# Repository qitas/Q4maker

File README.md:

# [Q4maker](https://github.com/qitas/Q4maker) 

自定义3D打印机版本，包括arduino的4喷头装置和STM32升级版本

相关资源参考：

* [Marlin](https://github.com/MuellerDominik/Marlin) 
* [硬件设计](https://github.com/mnemocron/FHNW-Pro4E-FS19T8-3DPrinterBoard-STM32) 

## 锻造最美之器

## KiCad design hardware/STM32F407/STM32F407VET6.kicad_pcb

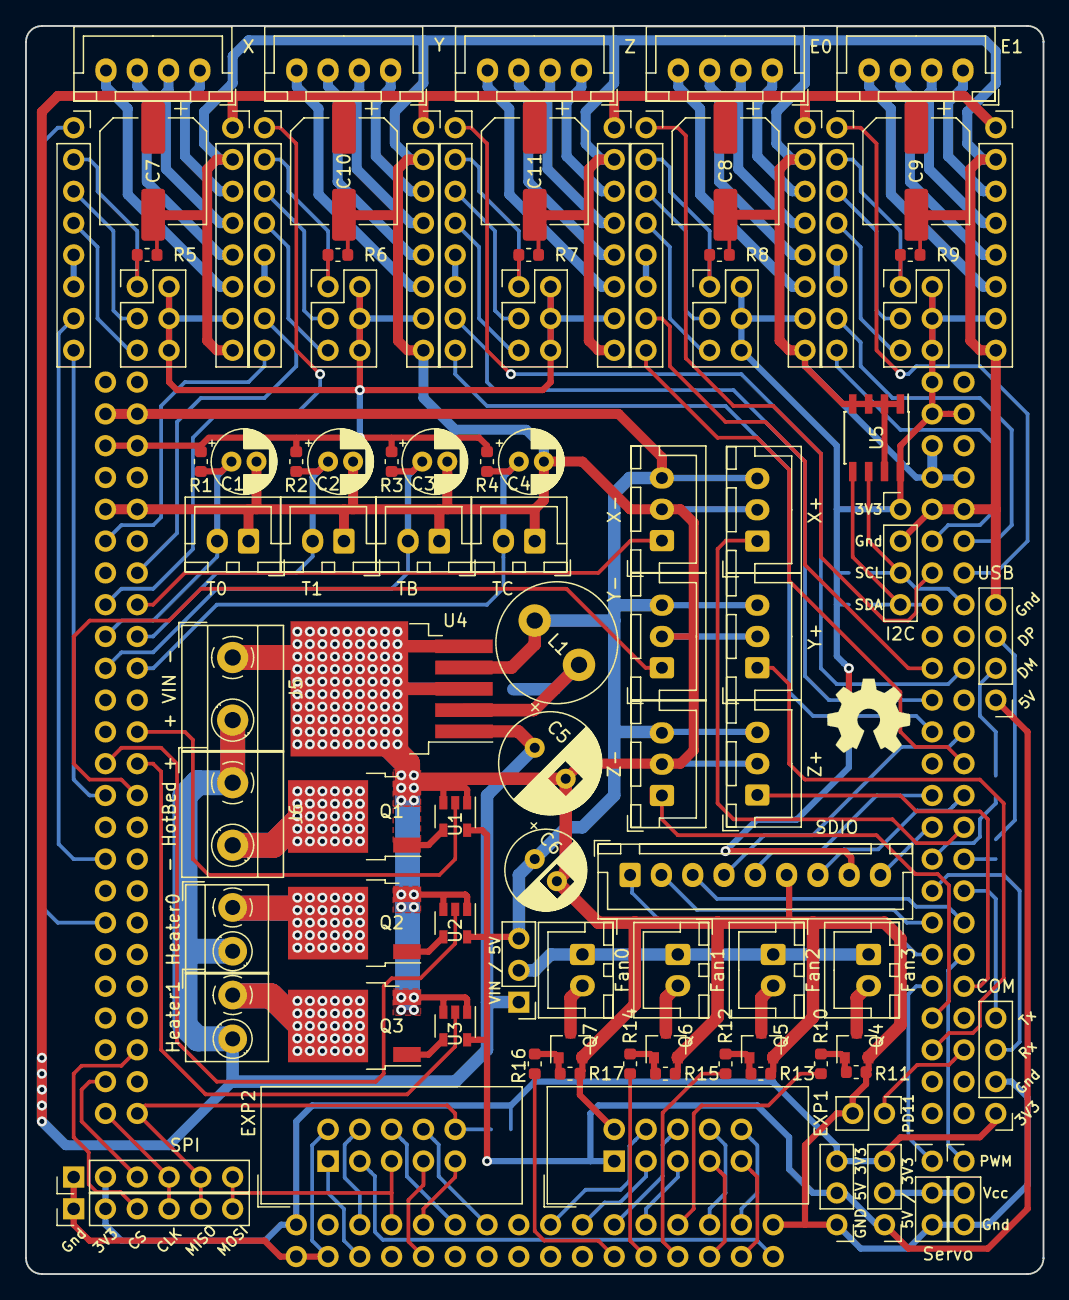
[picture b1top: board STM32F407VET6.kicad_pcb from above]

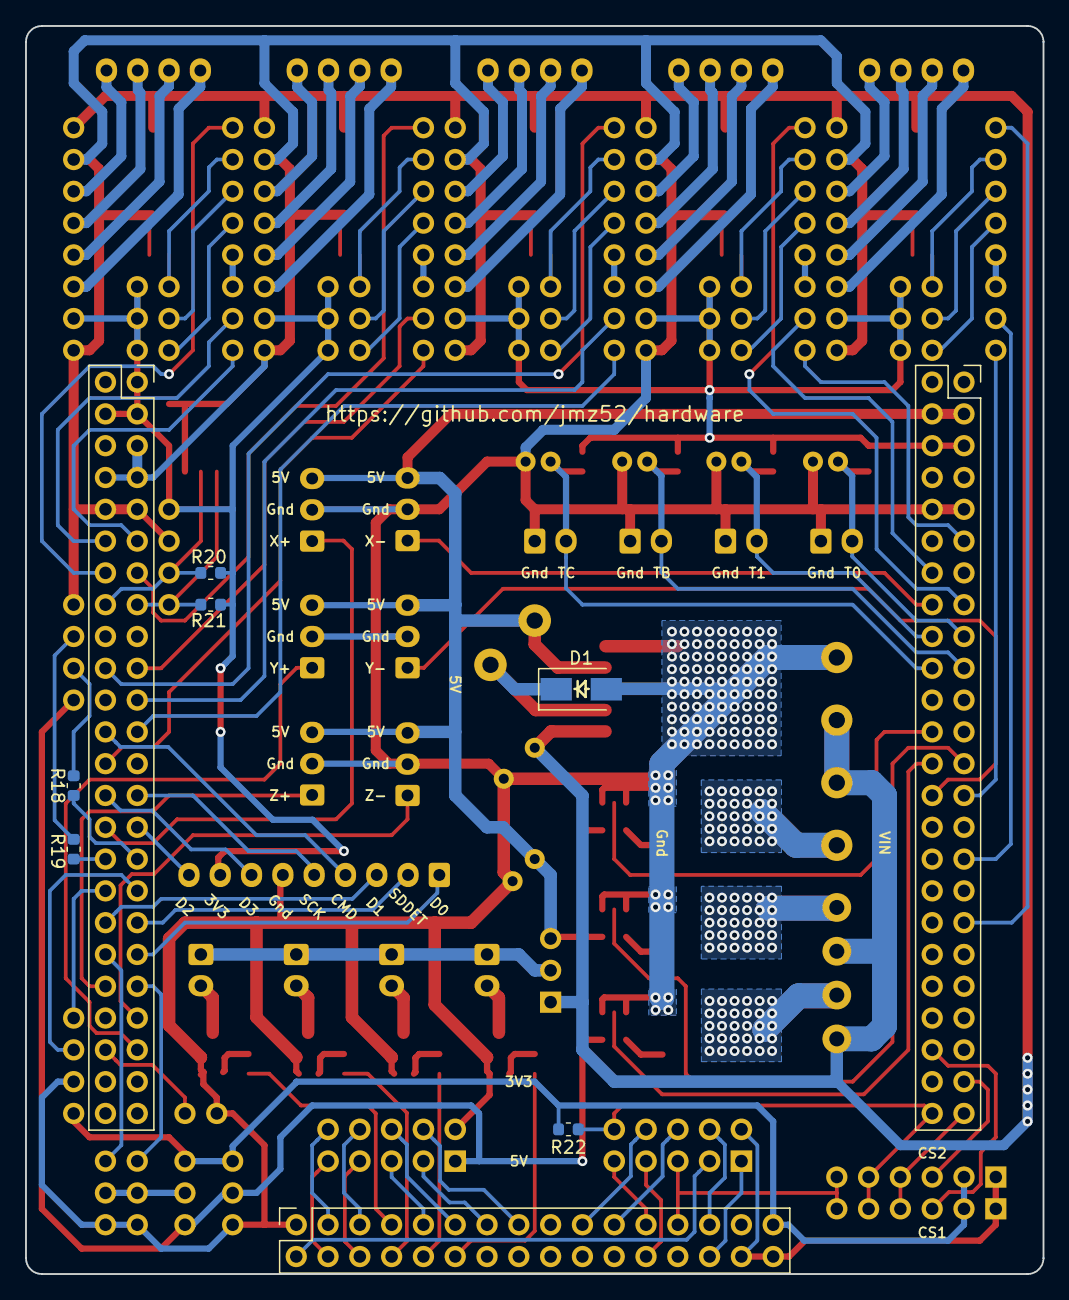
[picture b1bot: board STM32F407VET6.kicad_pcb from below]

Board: 2 copper layers, 81.3 x 99.7 mm, 102 parts (9 on the bottom side), 130 nets.

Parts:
C1, C2, C3, C4: 10uF 16V; CP_Radial_D5.0mm_P2.00mm
C5: 100uF 35V; CP_Radial_D8.0mm_P3.50mm
C6: 220uF 35V; CP_Radial_D6.3mm_P2.50mm
C7, C8, C9, C10, C11: 100uF 35V; CP_Elec_8x6.9
D1: SS14; D_SMA
J1: T0; JST_XH_B02B-XH-A_1x02_P2.50mm_Vertical
J2: T1; JST_XH_B02B-XH-A_1x02_P2.50mm_Vertical
J3: TB; JST_XH_B02B-XH-A_1x02_P2.50mm_Vertical
J4: TC; JST_XH_B02B-XH-A_1x02_P2.50mm_Vertical
J5: + VIN -; TerminalBlock_MetzConnect_Type055_RT01502HDWU_1x02_P5.00mm_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
J6: - HotBed +; TerminalBlock_MetzConnect_Type055_RT01502HDWU_1x02_P5.00mm_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
J7: Heater0; TerminalBlock_MetzConnect_Type059_RT06302HBWC_1x02_P3.50mm_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
J8: Heater1; TerminalBlock_MetzConnect_Type059_RT06302HBWC_1x02_P3.50mm_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
J9: Fan3; JST_XH_B02B-XH-A_1x02_P2.50mm_Vertical
J10: Fan2; JST_XH_B02B-XH-A_1x02_P2.50mm_Vertical
J11: Fan1; JST_XH_B02B-XH-A_1x02_P2.50mm_Vertical
J12: X_logic; PinSocket_1x08_P2.54mm_Vertical
J13, J22, J26, J29, J32: Microsteps; PinHeader_2x03_P2.54mm_Vertical
J14: X-; JST_XH_B03B-XH-A_1x03_P2.50mm_Vertical
J15: Y-; JST_XH_B03B-XH-A_1x03_P2.50mm_Vertical
J16: Z-; JST_XH_B03B-XH-A_1x03_P2.50mm_Vertical
J17: Left; PinSocket_2x24_P2.54mm_Vertical
J18: Y_logic; PinSocket_1x08_P2.54mm_Vertical
J19: X+; JST_XH_B03B-XH-A_1x03_P2.50mm_Vertical
J20: Y+; JST_XH_B03B-XH-A_1x03_P2.50mm_Vertical
J21: Z+; JST_XH_B03B-XH-A_1x03_P2.50mm_Vertical
J23: EXP2; IDC-Header_2x05_P2.54mm_Vertical
J24: Z_logic; PinSocket_1x08_P2.54mm_Vertical
J25: Bottom; PinSocket_2x16_P2.54mm_Vertical
J27: EXP1; IDC-Header_2x05_P2.54mm_Vertical
J28: E0_logic; PinSocket_1x08_P2.54mm_Vertical
J30: Right; PinSocket_2x24_P2.54mm_Vertical
J31: E1_logic; PinSocket_1x08_P2.54mm_Vertical
J33: X_motor; PinSocket_1x08_P2.54mm_Vertical
J34: Y_motor; PinSocket_1x08_P2.54mm_Vertical
J35: Z_motor; PinSocket_1x08_P2.54mm_Vertical
J36: E0_motor; PinSocket_1x08_P2.54mm_Vertical
J37: E1_motor; PinSocket_1x08_P2.54mm_Vertical
J38: X; JST_XH_B04B-XH-A_1x04_P2.50mm_Vertical
J39: Y; JST_XH_B04B-XH-A_1x04_P2.50mm_Vertical
J40: Z; JST_XH_B04B-XH-A_1x04_P2.50mm_Vertical
J41: E0; JST_XH_B04B-XH-A_1x04_P2.50mm_Vertical
J42: E1; JST_XH_B04B-XH-A_1x04_P2.50mm_Vertical
J43: Fan0; JST_XH_B02B-XH-A_1x02_P2.50mm_Vertical
J44: COM; PinHeader_1x04_P2.54mm_Vertical
J45: USB; PinHeader_1x04_P2.54mm_Vertical
J47: I2C; PinHeader_1x04_P2.54mm_Vertical
J48, J49: SPI; PinHeader_1x06_P2.54mm_Vertical
J50: SDIO; JST_XH_B09B-XH-A_1x09_P2.50mm_Vertical
J51, J52: Servo; PinHeader_1x03_P2.54mm_Vertical
J53: PowerSelect; PinHeader_1x03_P2.54mm_Vertical
J54, J56: Power; PinHeader_1x03_P2.54mm_Vertical
J55: PD11; PinHeader_1x02_P2.54mm_Vertical
L1: 47uH; L_Radial_D9.5mm_P5.00mm_Fastron_07HVP
Q1, Q2, Q3: Q_NMOS_GDS; TO-252-2
Q4, Q5, Q6, Q7: Q_NMOS_GSD; SOT-23
R1, R2, R3, R4, R5, R6, R7, R8, R9, R20, R21, R22: 4K7; R_0603_1608Metric
R10, R12, R14, R16: 10; R_0603_1608Metric
R11, R13, R15, R17: 10K; R_0603_1608Metric
R18, R19: 22R; R_0603_1608Metric
U1, U2, U3: SN74AHC; SOT-23-5
U4: LM2596S-5; TO-263-5_TabPin3
U5: AT24CS01-SSHM; SOIC-8_3.9x4.9mm_P1.27mm

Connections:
3V3: J13.2, J13.4, J13.6, J17.5, J17.6, J17.7, J17.8, J17.22, J22.2, J22.4, J22.6, J25.31, J26.2, J26.4, J26.6, J29.2, J29.4, J29.6, J30.1, J30.2, J30.3, J30.4, J32.2, J32.4, J32.6, J33.7, J34.7, J35.7, J36.7, J37.7, J44.1, J47.1, J48.2, J49.2, J50.8, J53.3, J54.3, R1.1, R2.1, R3.1, R4.1, R20.1, R21.2, R22.2, U5.8
5V: C6.1, J14.3, J15.3, J16.3, J17.1, J17.2, J17.3, J17.4, J19.3, J20.3, J21.3, J27.1, J45.1, J53.1, J54.2, J56.3, L1.2, U1.5, U2.5, U3.5, U4.4
12V: C5.1, C7.1, C8.1, C9.1, C10.1, C11.1, J5.2, J6.1, J7.2, J8.2, J33.1, J34.1, J35.1, J36.1, J37.1, J56.1, U4.1
Abort: J23.1, J25.28
Beeper: J25.3, J27.10
CLK: J17.47, J23.9, J25.23, J48.4, J49.4
E0_Dir: J28.8, J30.26
E0_En: J28.1, J30.13
E0_Step: J28.7, J30.19
E1_Dir: J30.11, J31.8
E1_En: J30.14, J31.1
E1_Step: J30.12, J31.7
EN1: J23.8, J25.19
EN2: J23.6, J25.21
ENC: J25.4, J27.9
Fan0: J25.12, R16.2
Fan1: J25.10, R14.2
Fan2: J25.8, R12.2
Fan3: J25.7, R10.2
GND: C1.2, C2.2, C3.2, C4.2, C5.2, C6.2, C7.2, C8.2, C9.2, C10.2, C11.2, D1.2, J1.1, J2.1, J3.1, J4.1, J5.1, J14.2, J15.2, J16.2, J17.9, J17.10, J17.21, J19.2, J20.2, J21.2, J23.2, J25.1, J25.30, J25.32, J27.2, J30.5, J30.7, J30.8, J30.9, J30.10, J33.2, J33.8, J34.2, J34.8, J35.2, J35.8, J36.2, J36.8, J37.2, J37.8, J44.2, J45.4, J47.2, J48.1, J49.1, J50.6, J51.3, J52.3, J54.1, J55.2, Q1.3, Q2.3, Q3.3, Q4.2, Q5.2, Q6.2, Q7.2, R5.1, R6.1, R7.1, R8.1, R9.1, R11.1, R13.1, R15.1, R17.1, U1.1, U1.3, U2.1, U2.3, U3.1, U3.3, U4.3, U4.5, U5.1, U5.2, U5.3, U5.4, U5.7
Heater0: J17.25, U2.2
Heater1: J17.26, U3.2
HotBed: J17.24, U1.2
LCD4: J25.11, J27.6
LCD5: J25.9, J27.5
LCD6: J25.15, J27.4
LCD7: J25.13, J27.3
LCDE: J25.5, J27.8
LCDRS: J25.6, J27.7
MISO: J17.48, J23.10, J25.26, J48.5, J49.5, R22.1
MOSI: J23.5, J25.25, J48.6, J49.6
unnamed: D1.1, L1.1, U4.2
unnamed: J6.2, Q1.2
unnamed: J7.1, Q2.2
unnamed: J8.1, Q3.2
unnamed: J9.2, Q4.3
unnamed: J9.1, J10.1, J11.1, J43.1, J56.2
unnamed: J10.2, Q5.3
unnamed: J11.2, Q6.3
unnamed: J12.2, J13.1, R5.2
unnamed: J12.3, J13.3
unnamed: J12.4, J13.5
unnamed: J12.5, J12.6
unnamed: J18.2, J22.1, R6.2
unnamed: J18.3, J22.3
unnamed: J18.4, J22.5
unnamed: J18.5, J18.6
unnamed: J24.2, J26.1, R7.2
unnamed: J24.3, J26.3
unnamed: J24.4, J26.5
unnamed: J24.5, J24.6
unnamed: J28.2, J29.1, R8.2
unnamed: J28.3, J29.3
unnamed: J28.4, J29.5
unnamed: J28.5, J28.6
unnamed: J31.2, J32.1, R9.2
unnamed: J31.3, J32.3
unnamed: J31.4, J32.5
unnamed: J31.5, J31.6
unnamed: J33.3, J38.1
unnamed: J33.4, J38.2
unnamed: J33.5, J38.3
unnamed: J33.6, J38.4
unnamed: J34.3, J39.1
unnamed: J34.4, J39.2
unnamed: J34.5, J39.3
unnamed: J34.6, J39.4
unnamed: J35.3, J40.1
unnamed: J35.4, J40.2
unnamed: J35.5, J40.3
unnamed: J35.6, J40.4
unnamed: J36.3, J41.1
unnamed: J36.4, J41.2
unnamed: J36.5, J41.3
unnamed: J36.6, J41.4
unnamed: J37.3, J42.1
unnamed: J37.4, J42.2
unnamed: J37.5, J42.3
unnamed: J37.6, J42.4
unnamed: J43.2, Q7.3
unnamed: J45.2, R18.2
unnamed: J45.3, R19.2
unnamed: J51.2, J52.2, J53.2
unnamed: Q1.1, U1.4
unnamed: Q2.1, U2.4
unnamed: Q3.1, U3.4
unnamed: Q4.1, R10.1, R11.2
unnamed: Q5.1, R12.1, R13.2
unnamed: Q6.1, R14.1, R15.2
unnamed: Q7.1, R16.1, R17.2
PD11: J30.44, J55.1
PWM1: J30.39, J52.1
PWM2: J30.38, J51.1
RX: J30.33, J44.3
Reset: J23.3, J25.2
SCL: J30.16, J47.3, R20.2, U5.6
SDA: J30.15, J47.4, R21.1, U5.5
SDDET: J23.4, J25.27
SDIO_CMD: J30.24, J50.4
SDIO_D0: J30.37, J50.1
SDIO_D1: J30.36, J50.3
SDIO_D2: J30.29, J50.9
SDIO_D3: J30.28, J50.7
SDIO_DET: J30.35, J50.2
SDIO_SCK: J30.27, J50.5
SDSS: J23.7, J25.24
SS1: J17.44, J48.3
SS2: J17.45, J49.3
T0: C1.1, J1.2, J17.17, R1.2
T1: C2.1, J2.2, J17.18, R2.2
TB: C3.1, J3.2, J17.19, R3.2
TC: C4.1, J4.2, J17.20, R4.2
TX: J30.34, J44.4
USB_DM: J30.31, R18.1
USB_DP: J30.32, R19.1
X+: J19.1, J30.30
X-: J14.1, J17.16
X_Dir: J12.8, J17.27
X_En: J12.1, J17.35
X_Step: J12.7, J17.31
Y+: J20.1, J30.43
Y-: J15.1, J17.28
Y_Dir: J17.11, J18.8
Y_En: J17.15, J18.1
Y_Step: J17.14, J18.7
Z+: J21.1, J30.40
Z-: J16.1, J30.41
Z_Dir: J24.8, J30.23
Z_En: J24.1, J30.20
Z_Step: J24.7, J30.21

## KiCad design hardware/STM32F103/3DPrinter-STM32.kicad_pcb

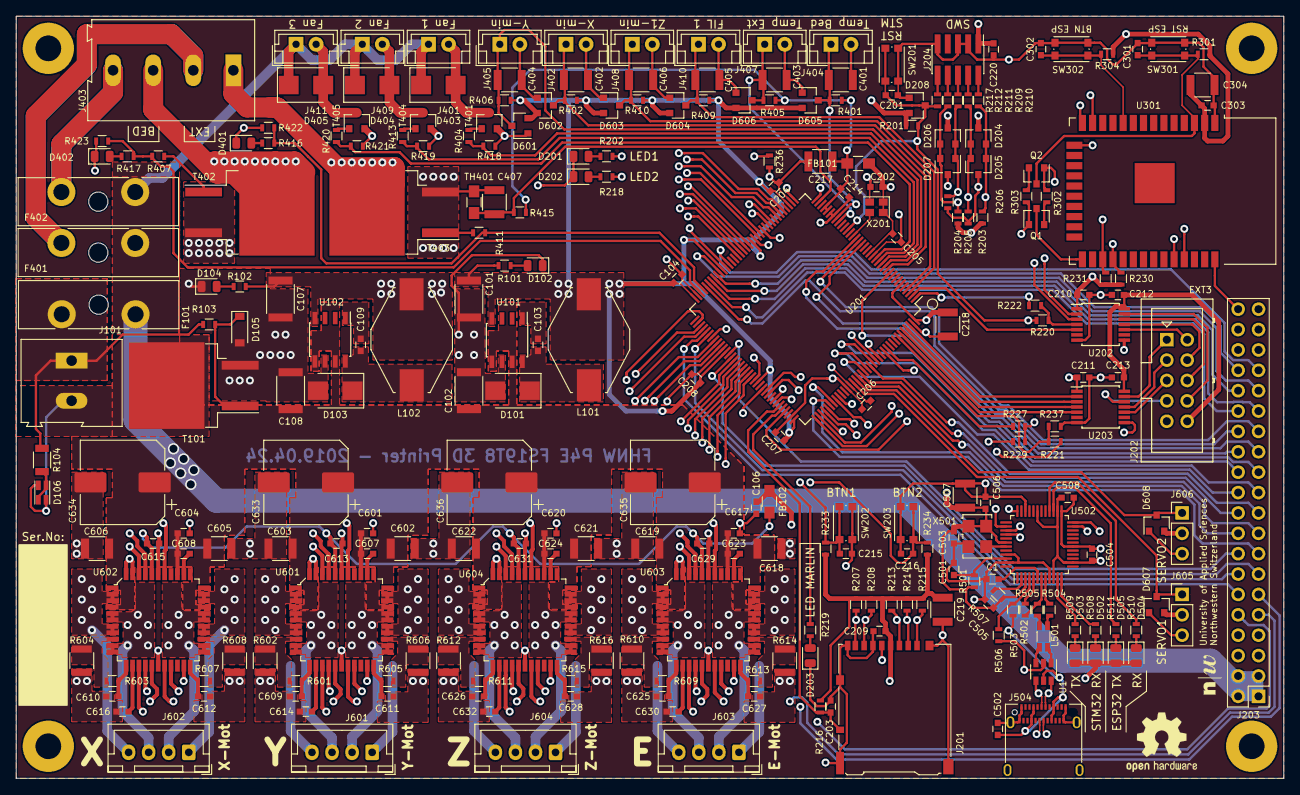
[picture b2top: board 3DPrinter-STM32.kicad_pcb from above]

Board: 4 copper layers, 158.0 x 95.0 mm, 264 parts (0 on the bottom side), 212 nets.

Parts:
C1: 33n; C_0603
C101, C107: 100uF; C_1812
C102, C108: 330uF; C_1812
C103, C109: 0.01uF/50V; C_0603
C104, C106, C201, C202, C203, C204, C205, C206, C207, C208, C209, C210, C211, C212, C213, C215, C216, C220, C301, C302, C303, C501, C502, C503, C504, C505, C506, C508, C601, C604, C609, C610, C611, C612, C613, C615, C617, C620, C625, C626, C627, C628, C629, C631: 100n; C_0603
C214: 10n; C_0603
C217: 1u; C_1210
C218, C219, C304, C401, C402, C403, C404, C405, C406, C407, C507, C602, C603, C605, C606, C618, C619, C621, C622: 10u; C_1210
C607, C608, C623, C624: 220n; C_0603
C614, C616, C630, C632: 470n; C_0603
C633, C634, C635, C636: 470u; CP_Elec_10x10
D101, D103, D403, D404, D405: Shottky STPS1L30A; D_SMB
D102, D104, D201: LED_GRN; LED_0805_2012Metric
D105: BZT52H-B7V5; D_SOD-123
D106: APHBM2012LSURKZGKC; LED_Kingbright_SMD4_2.0x1.25
D202, D203, D401, D402, D502, D503, D504, D505: LED_YEL; LED_0805_2012Metric
D204, D206: BAT54C; SOT-23
D205, D207: BAT54A; SOT-23
D208, D601, D602, D603, D604, D605, D606, D607, D608: BAT54S; SOT-23
F101: Fuse_20A; Fuseholder_Blade_ATO_Littelfuse_Pudenz_2_Pin
F401: Fuse_3A; Fuseholder_Blade_ATO_Littelfuse_Pudenz_2_Pin
F402: Fuse_10A; Fuseholder_Blade_ATO_Littelfuse_Pudenz_2_Pin
FB101, FB102: Ferrite; R_0805_HandSoldering
G101: SYM_Serial_No; Label_Serial_Number_6x20
G102: SYM_FHNW_Logo; Logo_FHNW_03x05mm
H101, H102, H103, H104: MountingHole; MountingHole_3.2mm_M3_Pad
J101: Screw_Terminal_01x02; TerminalBlock_Altech_AK300-2_P5.00mm
J201: Micro_SD_Card_Det; microSD_HC_Hirose_DM3AT-SF-PEJM5
J202: Conn_02x05_Odd_Even; Multicomp_MC9A12-1034_2x05_P2.54mm_Vertical
J203: Conn_02x20_Odd_Even; PinHeader_2x20_P2.54mm_Vertical
J204: Conn_ARM_JTAG_SWD_10; PinHeader_2x05_P1.27mm_Vertical_SMD
J401, J402, J404, J405, J407, J408, J409, J410, J411: Conn_01x02; JST_EH_B02B-EH-A_02x2.50mm_Straight
J403: Screw_Terminal_01x04; TerminalBlock_Altech_AK300-4_P5.00mm
J504: USB_C_Receptacle; USB_C_Receptacle_Amphenol_12401610E4-2A
J601, J602, J603, J604: B4B-XH-A; JST_XH_B4B-XH-A_1x04_P2.50mm_Vertical
J605, J606: Conn_01x03; PinHeader_1x03_P2.54mm_Vertical
L101, L102: 47uH DO3316-473; L_Fastron_PISN_Handsoldering
L501: WE-744232090; WURTH_USB_Chocke_4PAD
LOGO101: OSHW-LOGOM-COPPER; OSHW-Logo2_9.8x8mm_SilkScreen
Q1, Q2: 2N3904; SOT-23
R101, R102, R202, R218, R219, R416, R417, R508, R509, R510, R511: 330R; R_0603
R103, R418, R419, R421, R422, R423: 100k; R_0603
R104: 10k; R_1206
R201, R203, R204, R205, R206, R207, R208, R213, R214, R215, R216, R230, R231, R233, R234, R236, R237, R301, R302, R303, R304, R402, R406, R407, R409, R410, R411, R506, R507: 10k; R_0603
R209, R210, R211, R212, R217: 100R; R_0603
R220, R221, R222, R227, R229: 0R; R_0603
R401, R405, R415, R503: 4k7; R_0603
R404, R413, R420: 180R; R_0603
R501: 470R; R_0603
R502: 1k5; R_0603
R504, R505: 27R; R_0603
R601, R603, R605, R607, R609, R611, R613, R615: 10R; R_0603
R602, R604, R606, R608, R610, R612, R614, R616: 0R15; R_1210
SW201, SW202, SW203, SW301, SW302: SW_Push; SW_SPST_KMR2
T101, T402, T403: BUK963R3-60E; TO-263-2
T401, T404, T405: PMV40UN2; SOT-23
TH401: Thermistor_NTC; R_0805_HandSoldering
U1: USBLC6-2SC6; SOT-23-6
U101: LM2675M-3.3; SOIC-8_3.9x4.9mm_P1.27mm
U102: LM2675M-5; SOIC-8_3.9x4.9mm_P1.27mm
U201: STM32F103ZETx; LQFP-144_20x20mm_Pitch0.5mm
U202, U203: NTS0104PW-Q100J; TSSOP-14_4.4x5mm_Pitch0.65mm
U301: ESP32-WROOM-32
U502: FT2232D; LQFP-48_7x7mm_P0.5mm
U601, U602, U603, U604: TMC2660; TQFP-44_10x10mm
X201: SG-210STF; Oscillator_SMD_SeikoEpson_SG210-4Pin_2.5x2.0mm
X501: SG5032CCN-6.000000M-HJGA3; Oscillator_SMD_SeikoEpson_SG8002LB-4Pin_5.0x3.2mm

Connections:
+3.3VA: C214.1, C217.1, FB101.1, R401.1, R405.1, R415.1, U201.32, U201.33
+3.3VP: C613.1, C615.1, C629.1, C631.1, FB102.1, U601.40, U602.40, U603.40, U604.40
+3V3: C101.1, C104.1, C106.1, C202.1, C204.1, C205.1, C206.1, C207.1, C208.1, C209.1, C210.1, C211.1, C218.1, C219.1, C220.1, C303.1, C304.1, C504.1, C508.1, D204.3, D206.3, D208.2, D502.2, D503.2, D504.2, D505.2, D601.2, D602.2, D603.2, D604.2, D605.2, D606.2, D607.2, D608.2, FB101.2, FB102.2, J201.4, J203.7, J203.8, J204.1, J605.2, J606.2, L101.2, R101.1, R201.1, R203.2, R204.2, R207.1, R208.1, R213.1, R214.1, R215.1, R216.2, R230.1, R231.1, R233.1, R234.1, R301.1, R304.1, R402.1, R406.1, R409.1, R410.1, U101.4, U201.6, U201.17, U201.39, U201.52, U201.62, U201.72, U201.84, U201.95, U201.108, U201.121, U201.131, U201.144, U202.1, U202.8, U203.1, U203.8, U301.2, U502.10, U502.14, U502.26, U502.31, X201.1, X201.4
+5V: C107.1, C212.1, C213.1, C503.1, C505.1, C506.1, C507.1, J202.10, L102.2, R102.1, R501.2, R507.1, U102.4, U202.14, U203.14, U502.3, U502.42, X501.1, X501.4
+24V: C102.1, C108.1, C601.1, C602.1, C603.1, C604.1, C605.1, C606.1, C607.1, C608.1, C617.1, C618.1, C619.1, C620.1, C621.1, C622.1, C623.1, C624.1, C633.1, C634.1, C635.1, C636.1, D403.1, D404.1, D405.1, F101.1, F401.2, F402.2, J203.1, J203.2, J203.3, J203.4, J401.1, J409.1, J411.1, U101.5, U101.7, U102.5, U102.7, U601.4, U601.30, U601.36, U602.4, U602.30, U602.36, U603.4, U603.30, U603.36, U604.4, U604.30, U604.36
/24V_GND: D106.1, D106.3, J101.2, T101.2
/24V_IN: F101.2, J101.1, R103.1, R104.1
/appendix_ESP32/ESP32_GPIO0: Q1.3, U301.25
/appendix_ESP32/ESP32_RESET: C301.1, Q2.3, R301.2, SW301.2, U301.3
/appendix_ESP32/ESP_DTR: Q1.1, R303.2, U502.36
/appendix_ESP32/ESP_RTS: Q2.1, R302.2, U502.38
/appendix_ESP32/ESP_RX_STM: R231.2, U201.101, U301.27
/appendix_ESP32/ESP_RX_USB: U301.34, U502.40
/appendix_ESP32/ESP_TX_STM: R230.2, U201.102, U301.28
/appendix_ESP32/ESP_TX_USB: U301.35, U502.39
/appendix_SENSORS_POWER/ADC_TEMP_BED: C401.1, D605.3, J404.1, R401.2, U201.29
/appendix_SENSORS_POWER/ADC_TEMP_E1: C403.1, D606.3, J407.1, R405.2, U201.28
/appendix_SENSORS_POWER/ADC_TEMP_PCB: C407.1, R415.2, TH401.2, U201.35
/appendix_SENSORS_POWER/Bed_pwr: J403.3, T402.2
/appendix_SENSORS_POWER/E1_pwr: J403.1, T403.2
/appendix_SENSORS_POWER/Fan1_pwr: D403.2, J401.2, T401.3
/appendix_SENSORS_POWER/Fan2_pwr: D404.2, J409.2, T404.3
/appendix_SENSORS_POWER/Fan3_pwr: D405.2, J411.2, T405.3
/appendix_SENSORS_POWER/SERVO_1: D607.3, J605.1, U201.122
/appendix_SENSORS_POWER/SERVO_2: D608.3, J606.1, U201.123
/appendix_SENSORS_POWER/SW_End_Filament_1: C405.1, D604.3, J410.1, R409.2, U201.3
/appendix_SENSORS_POWER/SW_End_X: C402.1, D601.3, J402.1, R402.2, U201.11
/appendix_SENSORS_POWER/SW_End_Y: C404.1, D602.3, J405.1, R406.2, U201.12
/appendix_SENSORS_POWER/SW_End_Z: C406.1, D603.3, J408.1, R410.2, U201.4
/appendix_STM32F103/BED_ON: R407.2, R417.2, R423.1, U201.70
/appendix_STM32F103/CS_E1: U201.93, U603.18
/appendix_STM32F103/CS_X: U201.50, U602.18
/appendix_STM32F103/CS_Y: U201.57, U601.18
/appendix_STM32F103/CS_Z1: U201.88, U604.18
/appendix_STM32F103/DIR_E1: U201.90, U603.41
/appendix_STM32F103/DIR_X: U201.42, U602.41
/appendix_STM32F103/DIR_Y: U201.54, U601.41
/appendix_STM32F103/DIR_Z1: U201.81, U604.41
/appendix_STM32F103/E1_ON: R411.2, R416.2, R422.1, U201.69
/appendix_STM32F103/EN_E1: U201.92, U603.19
/appendix_STM32F103/EN_X: U201.49, U602.19
/appendix_STM32F103/EN_Y: U201.56, U601.19
/appendix_STM32F103/EN_Z1: U201.87, U604.19
/appendix_STM32F103/FAN1: R404.2, R418.1, U201.13
/appendix_STM32F103/FAN2: R413.2, R419.1, U201.14
/appendix_STM32F103/FAN3: R420.2, R421.1, U201.15
/appendix_STM32F103/RCC_OSC_IN: U201.23, X201.3
/appendix_STM32F103/STALL_E1: U201.91, U603.38
/appendix_STM32F103/STALL_X: U201.43, U602.38
/appendix_STM32F103/STALL_Y: U201.55, U601.38
/appendix_STM32F103/STALL_Z1: U201.82, U604.38
/appendix_STM32F103/STEP_E1: U201.89, U603.42
/appendix_STM32F103/STEP_X: U201.41, U602.42
/appendix_STM32F103/STEP_Y: U201.53, U601.42
/appendix_STM32F103/STEP_Z1: U201.80, U604.42
/appendix_STM32F103/STM32_BOOT_0: R221.1, U301.14
/appendix_STM32F103/STM32_NRST: R229.1, U301.13
/appendix_STM32F103/STM_BOOT0: R221.2, R237.1, U201.138
/appendix_STM32F103/STM_BOOT1: R236.1, U201.48
/appendix_TMC2660_X/MOT_E1_A1: J603.4, U603.2, U603.3, U603.7, U603.8
/appendix_TMC2660_X/MOT_E1_A2: J603.3, U603.5, U603.6, U603.10, U603.11
/appendix_TMC2660_X/MOT_E1_B1: J603.1, U603.26, U603.27, U603.31, U603.32
/appendix_TMC2660_X/MOT_E1_B2: J603.2, U603.23, U603.24, U603.28, U603.29
/appendix_TMC2660_X/MOT_X_A1: J602.4, U602.2, U602.3, U602.7, U602.8
/appendix_TMC2660_X/MOT_X_A2: J602.3, U602.5, U602.6, U602.10, U602.11
/appendix_TMC2660_X/MOT_X_B1: J602.1, U602.26, U602.27, U602.31, U602.32
/appendix_TMC2660_X/MOT_X_B2: J602.2, U602.23, U602.24, U602.28, U602.29
/appendix_TMC2660_X/MOT_Y_A1: J601.4, U601.2, U601.3, U601.7, U601.8
/appendix_TMC2660_X/MOT_Y_A2: J601.3, U601.5, U601.6, U601.10, U601.11
/appendix_TMC2660_X/MOT_Y_B1: J601.1, U601.26, U601.27, U601.31, U601.32
/appendix_TMC2660_X/MOT_Y_B2: J601.2, U601.23, U601.24, U601.28, U601.29
/appendix_TMC2660_X/MOT_Z1_A1: J604.4, U604.2, U604.3, U604.7, U604.8
/appendix_TMC2660_X/MOT_Z1_A2: J604.3, U604.5, U604.6, U604.10, U604.11
/appendix_TMC2660_X/MOT_Z1_B1: J604.1, U604.26, U604.27, U604.31, U604.32
/appendix_TMC2660_X/MOT_Z1_B2: J604.2, U604.23, U604.24, U604.28, U604.29
/appendix_UART_USB/FT_RX_A: U201.36, U502.23
/appendix_UART_USB/FT_TX_A: U201.37, U502.24
/appendix_UART_USB/USB_D_N: J504.A7, J504.B7, U1.6
/appendix_UART_USB/USB_D_P: J504.A6, J504.B6, U1.4
/appendix_UART_USB/USB_FT_D_N: R504.1, U502.8
/appendix_UART_USB/USB_FT_D_P: R502.2, R505.1, U502.7
/appendix_UART_USB/USB_SUP_D_N: L501.3, R504.2
/appendix_UART_USB/USB_SUP_D_P: L501.2, R505.2
/appendix_UART_USB/USB_TVS_D_N: L501.4, U1.1
/appendix_UART_USB/USB_TVS_D_P: L501.1, U1.3
/appendix_UART_USB/XTAL_FTDI: U502.43, X501.3
ADC_TEMP_EXT: J203.27, U201.21
BTN_USER_1: C215.1, R233.2, SW202.2, U201.79
BTN_USER_2: C216.1, R234.2, SW203.2, U201.97
E2_ADC_TEMP: J203.26, U201.22
E2_CS: J203.14, U201.78
E2_DIR: J203.18, U201.115
E2_EN: J203.20, U201.125
E2_END_FIL: J203.24, U201.129
E2_FAN1: J203.30, U201.67
E2_FAN2: J203.32, U201.65
E2_HOTEND: J203.34, U201.63
E2_STALL: J203.22, U201.126
E2_STEP: J203.16, U201.85
E3_ADC_TEMP: J203.25, U201.20
E3_CS: J203.13, U201.86
E3_DIR: J203.17, U201.124
E3_EN: J203.19, U201.128
E3_END_FIL: J203.23, U201.10
E3_STALL: J203.21, U201.127
E3_STEP: J203.15, U201.114
EXP3_LCD_Beeper: J202.1, U203.13
EXP3_LCD_CS: J202.7, U203.12
EXP3_LCD_Encoder_A: J202.5, U203.10
EXP3_LCD_Encoder_B: J202.3, U203.11
EXP3_LCD_Encoder_BTN: J202.2, U202.10
EXP3_LCD_MOSI: J202.8, U202.13
EXP3_LCD_Reset: J202.4, U202.11
EXP3_LCD_SCK: J202.6, U202.12
FAN_EXT: J203.28, U201.68
GND: C1.1, C101.2, C102.2, C104.2, C106.2, C107.2, C108.2, C201.2, C202.2, C203.2, C204.2, C205.2, C206.2, C207.2, C208.2, C209.2, C210.2, C211.2, C212.2, C213.2, C214.2, C215.2, C216.2, C217.2, C218.2, C219.2, C220.2, C301.2, C302.2, C303.2, C304.2, C401.2, C402.2, C403.2, C404.2, C405.2, C406.2, C407.2, C501.2, C502.2, C503.2, C504.2, C505.2, C506.2, C507.2, C508.2, C601.2, C602.2, C603.2, C604.2, C605.2, C606.2, C609.1, C610.1, C611.1, C612.1, C613.2, C614.2, C615.2, C616.2, C617.2, C618.2, C619.2, C620.2, C621.2, C622.2, C625.1, C626.1, C627.1, C628.1, C629.2, C630.2, C631.2, C632.2, C633.2, C634.2, C635.2, C636.2, D101.2, D102.1, D103.2, D104.1, D105.2, D201.1, D202.1, D203.1, D205.3, D207.3, D208.1, D401.1, D402.1, D601.1, D602.1, D603.1, D604.1, D605.1, D606.1, D607.1, D608.1, J201.6, J201.9, J201.11, J202.9, J203.35, J203.36, J203.37, J203.38, J203.39, J203.40, J204.3, J204.5, J204.9, J402.2, J404.2, J405.2, J407.2, J408.2, J410.2, J504.A1, J504.A12, J504.B1, J504.B12, J504.S1, J605.3, J606.3, R205.1, R206.1, R236.2, R237.2, R418.2, R419.2, R421.2, R422.2, R423.2, R506.1, R602.1, R604.1, R606.1, R608.1, R610.1, R612.1, R614.1, R616.1, SW201.1, SW202.1, SW203.1, SW301.1, SW302.1, T101.3, T401.2, T402.3, T403.3, T404.2, T405.2, TH401.1, U1.2, U101.6, U102.6, U201.16, U201.30, U201.31, U201.38, U201.51, U201.61, U201.71, U201.83, U201.94, U201.107, U201.120, U201.130, U201.143, U202.7, U203.7, U301.1, U301.15, U301.38, U502.9, U502.18, U502.25, U502.34, U502.45, U502.47, U601.17, U601.21, U601.39, U601.43, U601.44, U602.17, U602.21, U602.39, U602.43, U602.44, U603.17, U603.21, U603.39, U603.43, U603.44, U604.17, U604.21, U604.39, U604.43, U604.44, X201.2, X501.2
GPIO_EXT_0: J203.12, U201.77
GPIO_EXT_1: J203.29, U201.66
GPIO_EXT_2: J203.31, U201.64
GPIO_EXT_3: J203.33, U201.60
JTAG_RESET: C201.1, D208.3, R201.2, R217.2, R220.2, R227.2, R229.2, SW201.2, U201.25
JTAG_TCK_SWCLK: D204.1, D205.2, R205.2, R209.2, U201.109
JTAG_TDI: D206.1, D207.2, R204.1, R212.2, U201.110
JTAG_TDO_SWO: D206.2, D207.1, R206.2, R211.2, U201.133
JTAG_TMS_SWDIO: D204.2, D205.1, R203.1, R210.2, U201.105
JTAG_TRST: R227.1, U201.134
LCD_BUZZER: U201.142, U203.2
LCD_CS: U201.141, U203.3
LCD_ENC_A: U201.139, U203.5
LCD_ENC_B: U201.140, U203.4
LCD_ENC_BTN: U201.2, U202.5
LCD_Reset: R220.1, R222.1, U202.4
LED_Marlin: R219.1, U201.104
LED_USER_1: R202.1, U201.45
LED_USER_2: R218.1, U201.46
MISO: J203.10, U201.75, U601.14, U602.14, U603.14, U604.14
MOSI: J203.9, U201.76, U202.2, U601.15, U602.15, U603.15, U604.15
unnamed: C1.2, U502.6
unnamed: C103.1, U101.1
unnamed: C103.2, D101.1, L101.1, U101.8
unnamed: C109.1, U102.1
unnamed: C109.2, D103.1, L102.1, U102.8
unnamed: C302.1, R304.2, SW302.2, U301.10
unnamed: C501.1, R501.1, U502.46
unnamed: C607.2, U601.35
unnamed: C608.2, U602.35
unnamed: C609.2, R601.2, U601.12
unnamed: C610.2, R603.2, U602.12
unnamed: C611.2, R605.2, U601.22
unnamed: C612.2, R607.2, U602.22
unnamed: C614.1, U601.13
unnamed: C616.1, U602.13
unnamed: C623.2, U603.35
unnamed: C624.2, U604.35
unnamed: C625.2, R609.2, U603.12
unnamed: C626.2, R611.2, U604.12
unnamed: C627.2, R613.2, U603.22
unnamed: C628.2, R615.2, U604.22
unnamed: C630.1, U603.13
unnamed: C632.1, U604.13
unnamed: D102.2, R101.2
unnamed: D104.2, R102.2
unnamed: D105.1, R103.2, T101.1
unnamed: D106.2, D106.4, R104.2
unnamed: D201.2, R202.2
unnamed: D202.2, R218.2
unnamed: D203.2, R219.2
unnamed: D401.2, R416.1
unnamed: D402.2, R417.1
unnamed: D502.1, R508.2
unnamed: D503.1, R509.2
unnamed: D504.1, R510.2
unnamed: D505.1, R511.2
unnamed: F401.1, J403.2
unnamed: F402.1, J403.4
unnamed: J204.2, R210.1
unnamed: J204.4, R209.1
unnamed: J204.6, R211.1
unnamed: J204.8, R212.1
unnamed: J204.10, R217.1
unnamed: Q1.2, R302.1
unnamed: Q2.2, R303.1
unnamed: R222.2, U201.1
unnamed: R404.1, T401.1
unnamed: R407.1, T402.1
unnamed: R411.1, T403.1
unnamed: R413.1, T404.1
unnamed: R420.1, T405.1
unnamed: R502.1, U502.5
unnamed: R503.1, R506.2, U502.4
unnamed: R507.2, U502.2
unnamed: R601.1, R602.2, U601.9
unnamed: R603.1, R604.2, U602.9
unnamed: R605.1, R606.2, U601.25
unnamed: R607.1, R608.2, U602.25
unnamed: R609.1, R610.2, U603.9
unnamed: R611.1, R612.2, U604.9
unnamed: R613.1, R614.2, U603.25
unnamed: R615.1, R616.2, U604.25
SCK: J203.11, U201.74, U202.3, U601.16, U602.16, U603.16, U604.16
SD_CLK: J201.5, U201.113
SD_CMD: J201.3, R213.2, U201.116
SD_DAT0: J201.7, R208.2, U201.98
SD_DAT1: J201.8, R207.2, U201.99
SD_DAT2: J201.1, R215.2, U201.111
SD_DAT3: J201.2, R214.2, U201.112
SD_DETECT: C203.1, J201.10, R216.1, U201.103
UART1_RX_LED: R508.1, U502.12
UART1_TX_LED: R509.1, U502.11
UART2_RX_LED: R510.1, U502.28
UART2_TX_LED: R511.1, U502.27
VBUS: C502.1, J504.A4, J504.A9, J504.B4, J504.B9, R503.2, U1.5

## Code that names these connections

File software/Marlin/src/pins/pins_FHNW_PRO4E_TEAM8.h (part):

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 * 
 * EXP3, wrongly labeled as EXT3 on the board
 */
#define BEEPER_PIN          PE1     // EXP3-1 (J202-1) [LCD_Beeper]

#define BTN_EN1             PB8     // EXP3-5 (J202-5) [LCD_Encoder_A] [EXTI8]
#define BTN_EN2             PB9     // EXP3-3 (J202-3) [LCD_Encoder_B] [EXTI9]
#define BTN_ENC             PE3     // EXP3-2 (J202-2) [LCD_Encoder_BTN] [EXTI3]

#define LCD_PINS_RS         PE0     // EXP3-7 (J202-7) [LCD_CS]
#define LCD_PINS_ENABLE     PB15    // EXP3-8 (J202-8) [LCD_MOSI] / Fallback SW-SPI: PE2
#define LCD_PINS_D4         PB13    // EXP3-6 (J202-6) [LCD_SCK] / Fallback SW-SPI: PE6

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/**
 * SD card (uSD)
 */
#define SD_DETECT_PIN       PA11
#define SDSS                -1      // not required, SDIO interface is used
// #define LCD_SDSS            -1      // not present

/**
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 * Steppers
 */
#define X_ENABLE_PIN        PF11
#define X_STEP_PIN          PA5
#define X_DIR_PIN           PA6
#define X_CS_PIN            PF12
#define X_SG_PIN            PA7     // [EXTI7]

#define Y_ENABLE_PIN        PG0
#define Y_STEP_PIN          PF13
#define Y_DIR_PIN           PF14
#define Y_CS_PIN            PG1
#define Y_SG_PIN            PF15    // [EXTI15]

#define Z_ENABLE_PIN        PG2
#define Z_STEP_PIN          PD11
#define Z_DIR_PIN           PD12
#define Z_CS_PIN            PG3
#define Z_SG_PIN            PD13    // [EXTI13]

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#endif

#define E0_ENABLE_PIN       PG7
#define E0_STEP_PIN         PG4
#define E0_DIR_PIN          PG5
#define E0_CS_PIN           PG8
#define E0_SG_PIN           PG6     // [EXTI6]

// Second and third extruder
#if defined(EXPANSION_BOARD)
  // #define E1_ENABLE_PIN       PG10
  // #define E1_STEP_PIN         PD14
  // #define E1_DIR_PIN          PD1
  // #define E1_CS_PIN           PD9
  // #define E1_SG_PIN           PG11    // [EXTI11]

  // #define E2_ENABLE_PIN       PG13
  // #define E2_STEP_PIN         PD0
  // #define E2_DIR_PIN          PG9
  // #define E2_CS_PIN           PD15
  // #define E2_SG_PIN           PG12    // [EXTI12]
#endif

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 * Temperature sensors
 * 
 * Note: At the moment there is no possibility to use a temperature sensor located on the printer board.
 *       This implies that the following pins can't be used as intended: [ADC_TEMP_PCB, PA1] and [EXT_TEMP, PF9].
 */
#define TEMP_0_PIN          PC2     // [ADC]
#if defined(EXPANSION_BOARD)
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#endif
#define HEATER_BED_PIN      PB11

#define FAN_PIN             PF3     // [FAN1] used to cool the filament
#define E0_AUTO_FAN_PIN     PF4     // [FAN2] used to cool the hot end

#if defined(EXPANSION_BOARD)
  // #define FAN1_PIN            PE14    // [EXT1_FAN1] used to cool the filament
  // #define E1_AUTO_FAN_PIN     PE12    // [EXT1_FAN2] used to cool the hot end

  // #define FAN2_PIN            PE13    // [EXT2_FAN1] used to cool the filament
  // #define E2_AUTO_FAN_PIN     PE11    // [EXT2_FAN2] used to cool the hot end
#endif

// `USE_CONTROLLER_FAN` feature must be configured to use software PWM in `controllerfan.cpp`.
// To achieve this, the following line has to be removed: `analogWrite(CONTROLLER_FAN_PIN, speed);`.
#define CONTROLLER_FAN_PIN  PF5     // [FAN3] used to cool the FETs and the stepper drivers on the PCB

/**
 * Not implemented
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 * (FHNW pro4E Team8 board doesn't support this at the moment!)
 * 
 * Note: MKS Robin TFT screens may have different TFT controllers
 * If the screen stays white, disable 'LCD_RESET_PIN' to rely on the bootloader to do screen initialization.
 * 
 * Enabling 'LCD_RESET_PIN' causes flickering when entering the LCD menu due to LCD controller reset.
 * Reset feature was designed to "revive the LCD if static electricity killed it."
 */
#if defined(MKS_ROBIN_TFT)
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  // Data D0-D15 (PD14, PD15, PD0, PD1, PE7-PE15, PD8-PD10)
  // NOE: Read operation (PD4) / NWE: Write operation (PD5)
  // SPI2 (PB13, PB14, PB15) / Unknown (PB1, PC13)
  #define LCD_RESET_PIN       PF6     // Reset
  #define LCD_BACKLIGHT_PIN   PG11    // Backlight
  #define FSMC_CS_PIN         PG12    // NE4 (Chip Select)
  #define FSMC_RS_PIN         PF0     // A0 (LCD Register Select)
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
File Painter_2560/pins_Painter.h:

#if !defined(__AVR_ATmega1280__) && !defined(__AVR_ATmega2560__)
  #error "Oops!  Make sure you have 'Arduino Mega' selected from the 'Tools -> Boards' menu."
#endif

#ifndef BOARD_NAME
  #define BOARD_NAME "RAMPS For Painter"
  #define DEFAULT_MACHINE_NAME    "Painter"
  #define DEFAULT_SOURCE_CODE_URL "https://Qita.ltd/Painter"  
#endif

//A10-A15   D4/5/6/8/9/10
//16,17,23,25,27,29,31,33,35,37,38,41,43,45,47,32,42,44,4,5,6,11

#define HEATER_BED_PIN	    8
#define TEMP_BED_PIN       13            // ANALOG NUMBERING  

#define HEATER_0_PIN        9
#define TEMP_0_PIN         14            // ANALOG NUMBERING  

#define HEATER_1_PIN       10
#define TEMP_1_PIN         15            // ANALOG NUMBERING  

#define HEATER_2_PIN        4            // 4 5 6 IS ANOTHER 8 9 10
#define TEMP_2_PIN         11            // ANALOG NUMBERING  A15

#define HEATER_3_PIN        5 
#define TEMP_3_PIN         12            // ANALOG NUMBERING  A11

#define FAN_PIN             6            // PWM OUTPUT AROUND FANS 6
#define FAN1_PIN           32            // OUTPUT SWITCH FOR WATER FAN & WATER PUMP

#define SERVO0_PIN         11
#define PS_ON_PIN          12
#define LED_PIN            13 

#define FIL_RUNOUT_PIN     23         
#define FIL_1_RUNOUT_PIN   25
#define FIL_2_RUNOUT_PIN   27
#define FIL_3_RUNOUT_PIN   29

#define X_MIN_PIN           3
#define X_MAX_PIN           2
#define Y_MIN_PIN          14
#define Y_MAX_PIN          15
#define Z_MIN_PIN          18
#define Z_MAX_PIN          19

#define X_STEP_PIN         54
#define X_DIR_PIN          55
#define X_ENABLE_PIN       38

#define Y_STEP_PIN         60
#define Y_DIR_PIN          61
#define Y_ENABLE_PIN       56

#define Z_STEP_PIN         46
#define Z_DIR_PIN          48
#define Z_ENABLE_PIN       62     

#define E0_STEP_PIN        26
#define E0_DIR_PIN         28
#define E0_ENABLE_PIN      24

#define E1_STEP_PIN        36
#define E1_DIR_PIN         34
#define E1_ENABLE_PIN      30

#define E2_STEP_PIN        33
#define E2_DIR_PIN         35
#define E2_ENABLE_PIN      31

#define E3_STEP_PIN        43     
#define E3_DIR_PIN         41     
#define E3_ENABLE_PIN      37     

#define JoyStick_X          5      // ANALOG NUMBERING   A5
#define JoyStick_Y          9      // ANALOG NUMBERING   A9
#define JoyStick_Z         42      // DIGIT IO

#define HOME_PIN           44 
#define AIR_PIN            45
#define VACUUM_PIN         47

#define SD_DETECT_PIN      49
#define SDSS               53     

//#define CONTROLLERFAN_PIN  48


//#define WS8212A_PIN       4     // INNER
//#define WS8212B_PIN      45     // OUTER
//#define TOUCH_PIN        47     // TOUCH BTN
//#define KILL_PIN         41
//#define FILWIDTH_PIN      5              // ANALOG NUMBERING
//#define BEEPER_PIN                       // PWM OUTPUT  铚傞福鍣�
//#define MAIN_VOLTAGE_MEASURE_PIN    62   //Analogue PIN to measure the main voltage, with a 100k - 4k7 resitor divider.
//#define MAIN_WEIGHT_MEASURE_PIN     63   //Analogue PIN to measure the Weight

//#define SAFETY_TRIGGERED_PIN        28    //PIN to detect the safety circuit has triggered 鐢垫祦娴嬭瘯锛岄槻杩囨祦

//#define MOTOR_CURRENT_PWM_XY_PIN    46
//#define MOTOR_CURRENT_PWM_Z_PIN     47
//#define MOTOR_CURRENT_PWM_E_PIN     48

//Motor current PWM conversion, PWM value = MotorCurrentSetting * 255 / range
//#define MOTOR_CURRENT_PWM_RANGE   2000
//#define DEFAULT_PWM_MOTOR_CURRENT  {1300, 1300, 1250}

//#define BTN_EN1   40
//#define BTN_EN2   41
//#define BTN_ENC   19

//#if ENABLED(Z_PROBE_SLED)
   //  #define SLED_PIN         -1
//#endif

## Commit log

2017-06-05 init code from github
2017-06-06 my code
2018-10-12 add readme
2018-11-11 init
2018-11-11 add cura
2019-07-15 del cura
2019-07-15 fix link
2019-07-15 add hardware
2019-07-16 fix add software
2019-07-16 fix info
2019-07-16 add stm32f4 hardware
2019-07-29 fix monitor

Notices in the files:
software/Marlin/src/pins/pins_FHNW_PRO4E_TEAM8.h:
Copyright (C) 2019 MarlinFirmware [https://github.com/MarlinFirmware/Marlin]
Copyright (C) 2011 Camiel Gubbels / Erik van der Zalm
This program is free software: you can redistribute it and/or modify
it under the terms of the GNU General Public License as published by
the Free Software Foundation, either version 3 of the License, or
(at your option) any later version.
